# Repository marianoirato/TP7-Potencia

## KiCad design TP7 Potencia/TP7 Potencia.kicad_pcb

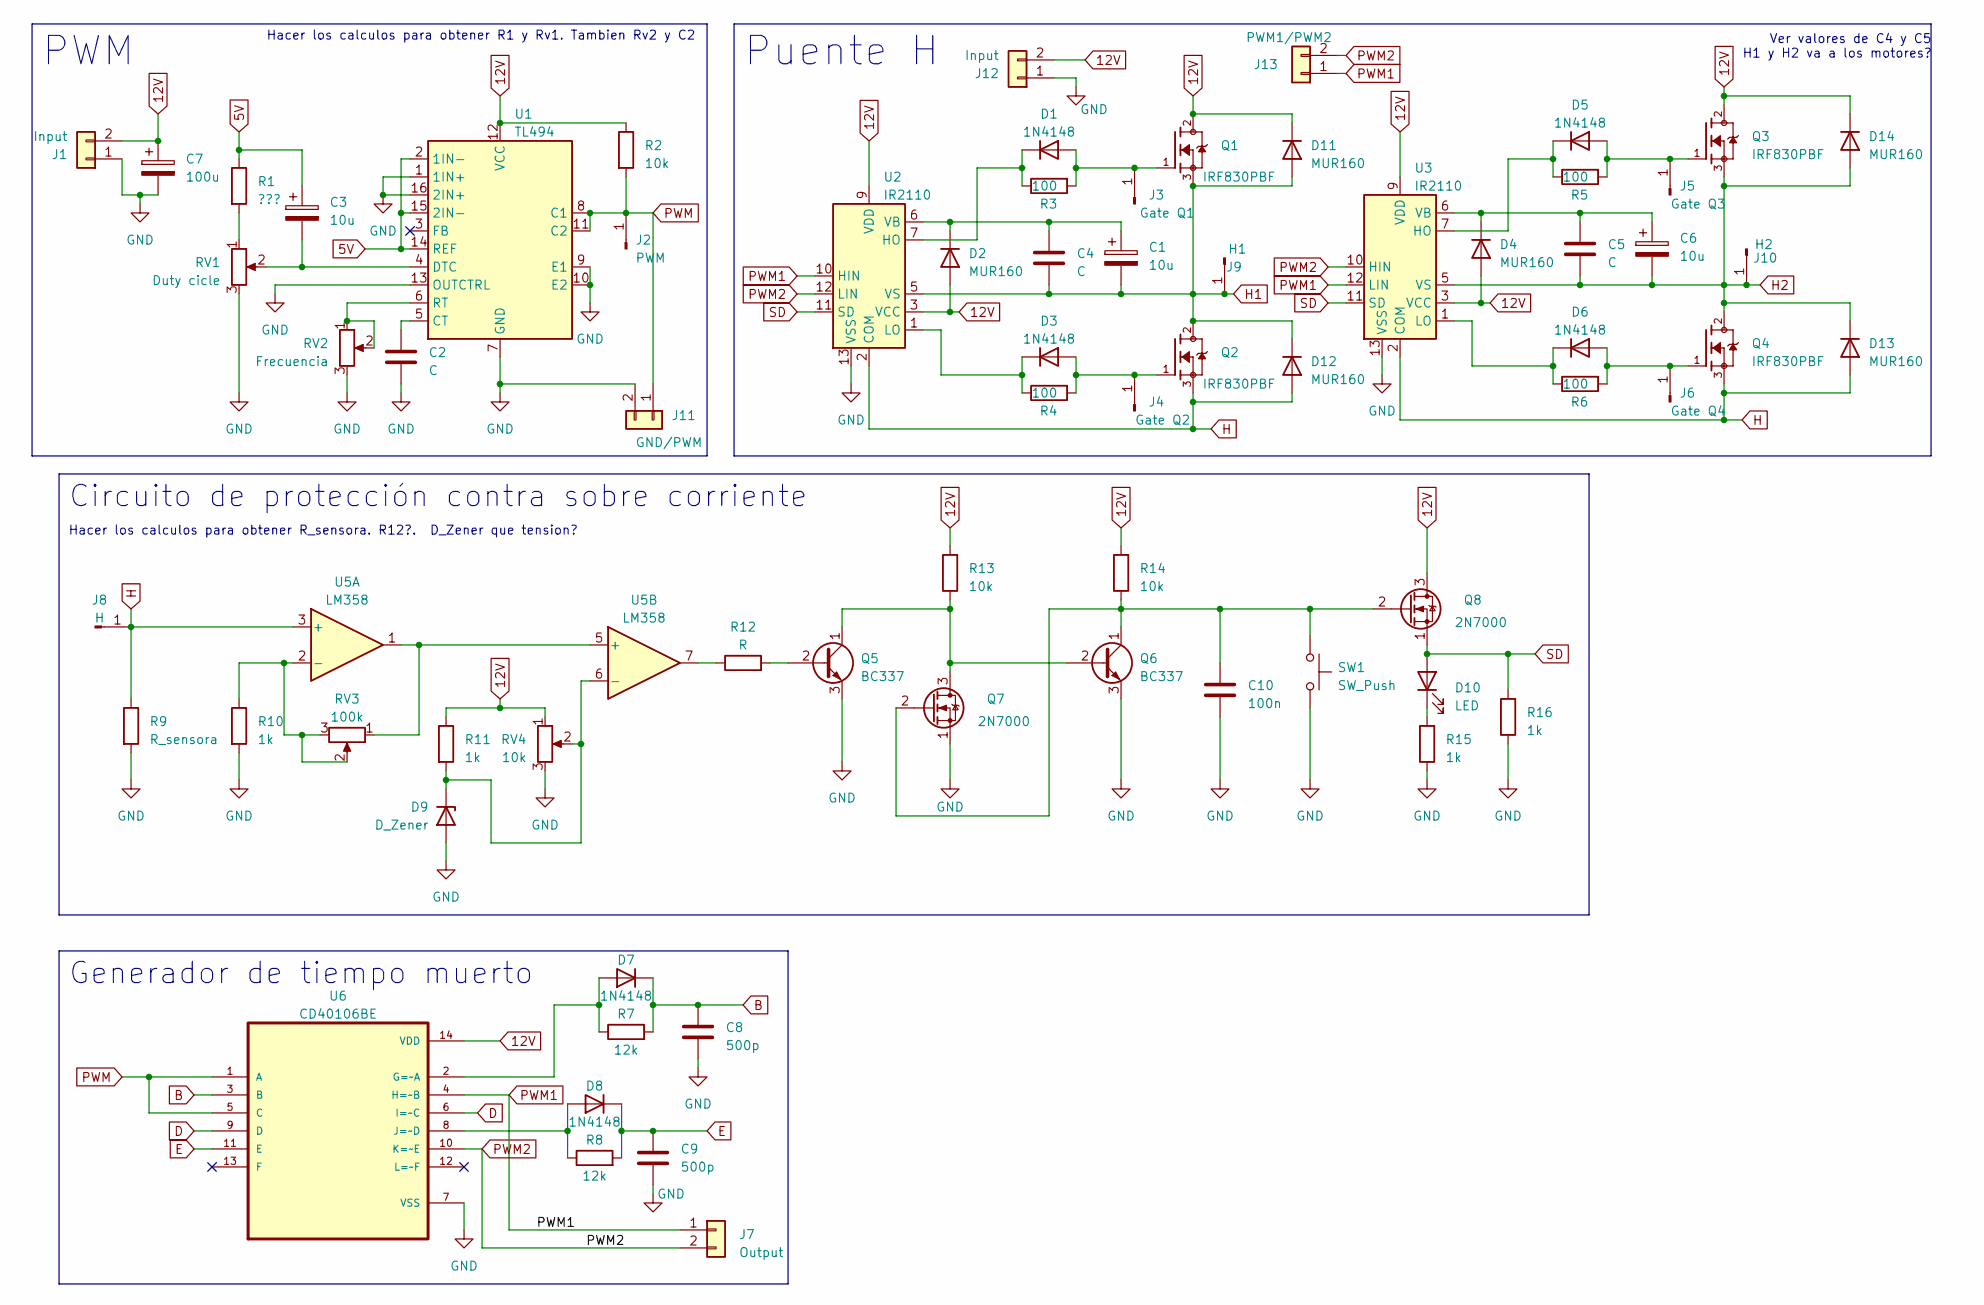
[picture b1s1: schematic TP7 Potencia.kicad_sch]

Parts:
C1, C3, C6: 10u; CP_Radial_D6.3mm_P2.50mm
C2, C4, C5: C; C_Disc_D3.0mm_W1.6mm_P2.50mm
C7: 100u; CP_Radial_D6.3mm_P2.50mm
C8, C9: 500p; C_Disc_D3.0mm_W1.6mm_P2.50mm
C10: 100n; C_Disc_D3.0mm_W1.6mm_P2.50mm
D1, D3, D5, D6, D7, D8: 1N4148; D_DO-35_SOD27_P7.62mm_Horizontal
D2, D4, D11, D12, D13, D14: MUR160; D_DO-35_SOD27_P7.62mm_Horizontal
D9: D_Zener; D_DO-35_SOD27_P7.62mm_Horizontal
D10: LED; LED_D3.0mm
J1, J12: Input; TerminalBlock_MetzConnect_Type011_RT05502HBWC_1x02_P5.00mm_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
J2: PWM; PinSocket_1x01_P2.54mm_Vertical
J3: Gate Q1; PinSocket_1x01_P2.54mm_Vertical
J4: Gate Q2; PinSocket_1x01_P2.54mm_Vertical
J5: Gate Q3; PinSocket_1x01_P2.54mm_Vertical
J6: Gate Q4; PinSocket_1x01_P2.54mm_Vertical
J7: Output; TerminalBlock_MetzConnect_Type011_RT05502HBWC_1x02_P5.00mm_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
J8: H; PinSocket_1x01_P2.54mm_Vertical
J9: H1; PinSocket_1x01_P2.54mm_Vertical
J10: H2; PinSocket_1x01_P2.54mm_Vertical
J11: GND/PWM; TerminalBlock_MetzConnect_Type011_RT05502HBWC_1x02_P5.00mm_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
J13: PWM1/PWM2; TerminalBlock_MetzConnect_Type011_RT05502HBWC_1x02_P5.00mm_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
Q1, Q2, Q3, Q4: IRF830PBF; TO254P1052X465X1989-3; PARTREV C
Q5, Q6: BC337; TO-92_Inline
Q7, Q8: 2N7000; TO-92_Inline
R1: ???; R_Axial_DIN0207_L6.3mm_D2.5mm_P10.16mm_Horizontal
R2, R13, R14: 10k; R_Axial_DIN0207_L6.3mm_D2.5mm_P10.16mm_Horizontal
R3, R4, R5, R6: 100; R_Axial_DIN0207_L6.3mm_D2.5mm_P10.16mm_Horizontal
R7, R8: 12k; R_Axial_DIN0207_L6.3mm_D2.5mm_P10.16mm_Horizontal
R9: R_sensora; R_Axial_DIN0207_L6.3mm_D2.5mm_P10.16mm_Horizontal
R10, R11, R15, R16: 1k; R_Axial_DIN0207_L6.3mm_D2.5mm_P10.16mm_Horizontal
R12: R; R_Axial_DIN0207_L6.3mm_D2.5mm_P10.16mm_Horizontal
RV1: Duty cicle; Potentiometer_Alps_RK163_Single_Horizontal
RV2: Frecuencia; Potentiometer_Bourns_3266Y_Vertical
RV3: 100k; Potentiometer_Bourns_3266Y_Vertical
RV4: 10k; Potentiometer_Bourns_3266Y_Vertical
SW1: SW_Push; SW_Push_2P1T_Toggle_CK_PVA1xxH1xxxxxxV2
U1: TL494; DIP-16_W7.62mm_Socket_LongPads
U2, U3: IR2110; DIP-14_W7.62mm
U5: LM358; DIP-8_W7.62mm_Socket_LongPads
U6: CD40106BE; DIP794W45P254L1969H508Q14

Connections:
5V: C3.1, R1.1, U1.2 (1IN-), U1.14 (REF), U1.15 (2IN-)
12V: C7.1, D2.2 (A), D4.2 (A), D11.1 (K), D14.1 (K), J1.2, J12.2, Q1.2, Q3.2, Q8.3 (D), R2.1, R11.1, R13.2, R14.2, RV4.1, U1.12 (VCC), U2.3 (VCC), U2.9 (VDD), U3.3 (VCC), U3.9 (VDD), U6.14 (VDD)
B: C8.1, D7.1 (K), R7.2, U6.3 (B)
D: U6.6 (I=~C), U6.9 (D)
E: C9.1, D8.1 (K), R8.2, U6.11 (E)
GND: C2.2, C7.2, C8.2, C9.2, C10.2, D9.2 (A), J1.1, J11.2, J12.1, Q5.3 (E), Q6.3 (E), Q7.1 (S), R9.2, R10.2, R15.1, R16.1, RV1.3, RV2.3, RV4.3, SW1.2, U1.1 (1IN+), U1.7 (GND), U1.9 (E1), U1.10 (E2), U1.13 (OUTCTRL), U1.16 (2IN+), U2.13 (VSS), U3.13 (VSS), U6.7 (VSS)
H: D12.2 (A), D13.2 (A), J8.1, Q2.3, Q4.3, R9.1, U2.2 (COM), U3.2 (COM), U5.3 (+)
H1: C1.2, C4.2, D11.2 (A), D12.1 (K), J9.1, Q1.3, Q2.2, U2.5 (VS)
H2: C5.2, C6.2, D13.1 (K), D14.2 (A), J10.1, Q3.3, Q4.2, U3.5 (VS)
unnamed: D1.2 (A), J3.1, Q1.1, R3.2
unnamed: D1.1 (K), R3.1, U2.7 (HO)
unnamed: C1.1, C4.1, D2.1 (K), U2.6 (VB)
unnamed: D3.2 (A), J4.1, Q2.1, R4.2
unnamed: D3.1 (K), R4.1, U2.1 (LO)
unnamed: C5.1, C6.1, D4.1 (K), U3.6 (VB)
unnamed: D5.2 (A), J5.1, Q3.1, R5.2
unnamed: D5.1 (K), R5.1, U3.7 (HO)
unnamed: D6.2 (A), J6.1, Q4.1, R6.2
unnamed: D6.1 (K), R6.1, U3.1 (LO)
unnamed: D7.2 (A), R7.1, U6.2 (G=~A)
unnamed: D8.2 (A), R8.1, U6.8 (J=~D)
unnamed: D9.1 (K), R11.2, RV4.2, U5.6 (-)
unnamed: D10.1 (K), R15.2
unnamed: Q5.2 (B), R12.2
unnamed: Q5.1 (C), Q6.2 (B), Q7.3 (D), R13.1
unnamed: C10.1, Q6.1 (C), Q7.2 (G), Q8.2 (G), R14.1, SW1.1
unnamed: R1.2, RV1.1
unnamed: R12.1, U5.7
unnamed: C2.1, U1.5 (CT)
unnamed: C3.2, RV1.2, U1.4 (DTC)
unnamed: RV2.1, RV2.2, U1.6 (RT)
unnamed: R10.1, RV3.2, RV3.3, U5.2 (-)
unnamed: RV3.1, U5.1, U5.5 (+)
PWM: J2.1, J11.1, R2.2, U1.8 (C1), U1.11 (C2), U6.1 (A), U6.5 (C)
PWM1: J7.1, J13.1, U2.10 (HIN), U3.12 (LIN), U6.4 (H=~B)
PWM2: J7.2, J13.2, U2.12 (LIN), U3.10 (HIN), U6.10 (K=~E)
SD: D10.2 (A), Q8.1 (S), R16.2, U2.11 (SD), U3.11 (SD)

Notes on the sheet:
Hacer los calculos para obtener R_sensora. R12?. D_Zener que tension?
Hacer los calculos para obtener R1 y Rv1. Tambien Rv2 y C2
Circuito de protección contra sobre corriente
Puente H
Generador de tiempo muerto
PWM
H1 y H2 va a los motores?
Ver valores de C4 y C5

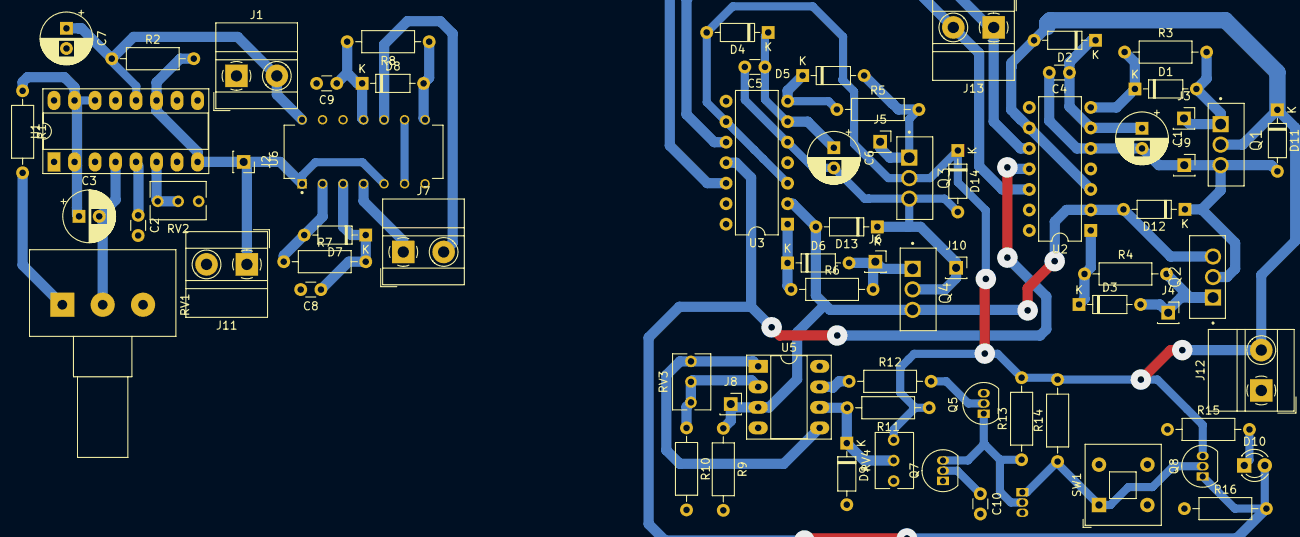
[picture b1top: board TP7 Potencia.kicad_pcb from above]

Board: 2 copper layers, 71 parts (1 on the bottom side), 37 nets.

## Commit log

2023-10-18 Agregado SCH
2023-10-19 Agregado footprints
2023-10-19 Placement de componentes en el PCB
2023-10-19 Ordenados los componentes por bloques
2023-10-19 Ruteo
2023-10-20 continuacion del rooteo y agregado de testpoint y borneras
2023-10-20 fin del rooteo
2023-10-20 corrección del fin de rooteo
